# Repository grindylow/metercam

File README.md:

# MeterCam

A WiFi "webcam" to monitor gas/water/electricity meters, or anything else that
needs regular (daily/weekly/monthly) inspection. When set to weekly intervals,
MeterCam will run on one set of AAA batteries for many years.

## Introduction

The MeterCam combines a standard ESP32-CAM module [1] (which works great, but
consumes a lot of power, even when sleeping) with custom hardware that only
powers up the camera module when it wants to take a picture, for example once
a day/week.

This custom hardware utilises a very energy-efficient "high-side power switch"
and a low-power microcontroller - keeping the power consumption during sleep
periods below 1 µW and resulting in battery lifetimes of many years.

## Features

- [ ] Configurable WiFi SSID/password
- [ ] Extended configuration options
- [ ] Configuration change via MQTT
- [ ] Image output via MQTT
- [ ] image acquisition on boot
- [ ] enable/disable "flash" LED
- [ ] Streaming video over HTTP (for setup)
- [ ] request shutdown

## Setup Instructions

The configuration web interface is based around XYZ's WifiManager[...].

A virgin MeterCam will enter configuration mode when first powered up.

Connect to the MeterCam WiFi Access Point (SSID "METERCAM", password:
"metercam") and configure all parameters as desired.

From now on, MeterCam will wake up at the configured intervals (see
[below](#operation)).

@todo you can force a configured MeterCam to go back into configuration mode
by setting jumper JPx. MeterCam will also fall back to configuration mode if
it hasn't been able to connect to the configured WiFi network five times in a
row (this is a feature of WifiManager).

## Operation

No maintenance is required during regular operation. MeterCam will

 1. wake up every interval
 2. connect to the configured WiFi
 3. take a picture
 4. transmit this picture via the configured means (MQTT, E-Mail, FTP, etc.)
 5. go back to sleep

@todo If MQTT is enabled, the MeterCam will subscribe to the configured "inbox" topic
and interpret incoming configuration requests.

## Detailed Description of MeterCam Components

### MeterCam Printed Circuit Board (PCB)

The MeterCam PCB contains a Microchip PIC16 microcontroller. It communicates
with the ESP32-CAM module via a bidirectional serial link. This link allows the
ESP32-CAM to request power-off and specific sleep durations.

The microcontroller also controls a "high-side power switch" used to cut power
to the ESP32-CAM module - thereby preventing the ESP32-CAM from consuming any
power during periods of inactivity.

### MeterCam µC Firmware

The software running on the MeterCam's microcontroller performs the following
tasks:

 - [ ] On initial bootup, switch *on* ESP32-CAM module, then wait for shutdown
   command .
 - [ ] Switch *off* ESP32-CAM module after 20 seconds, even if no
   (shutdown) command was received. Use a default sleep time of approximately 1 day in this case, if now other time has previously been configured.
 - [ ] Switch *off* ESP32-CAM when requested (via serial connection), and sleep
   for requested duration, consuming as little power as possible.
 - [ ] Switch *on* ESP32-CAM when requested sleep duration has passed.

ESP32-Firmware and µC-Firmware communicate via serial ports. The µC acts as the
slave and will respond to the following commands when transmitted by the ESP32:

| Command | Reply | Explanation |
|---------|-------|-------------|
| 'E' | 'e' | Echo request/reply - for testing the connection |
| 'A' <HI> <LO> | 'a' <HI> <LO> | Set new sleep time in 'intervals'. |
| 'S' | 's' | Switch off power to ESP32 'now' and sleep for configured sleep duration |

### MeterCam ESP32-CAM Firmware

Compile using Arduino Studio with ESP extensions and the following libraries:
 - ESP32-CAM
 - [WifiManager](https://github.com/tzapu/WiFiManager)
 - -[DoubleResetDetect](https://github.com/jenscski/DoubleResetDetect)-
 - [EspMQTTClient](https://github.com/plapointe6/EspMQTTClient), which requires...
   - [MQTT PubSubClient](https://github.com/knolleary/pubsubclient)
 - [ArduinoJSON](https://arduinojson.org/)

[1] ESP32-CAM module: ...

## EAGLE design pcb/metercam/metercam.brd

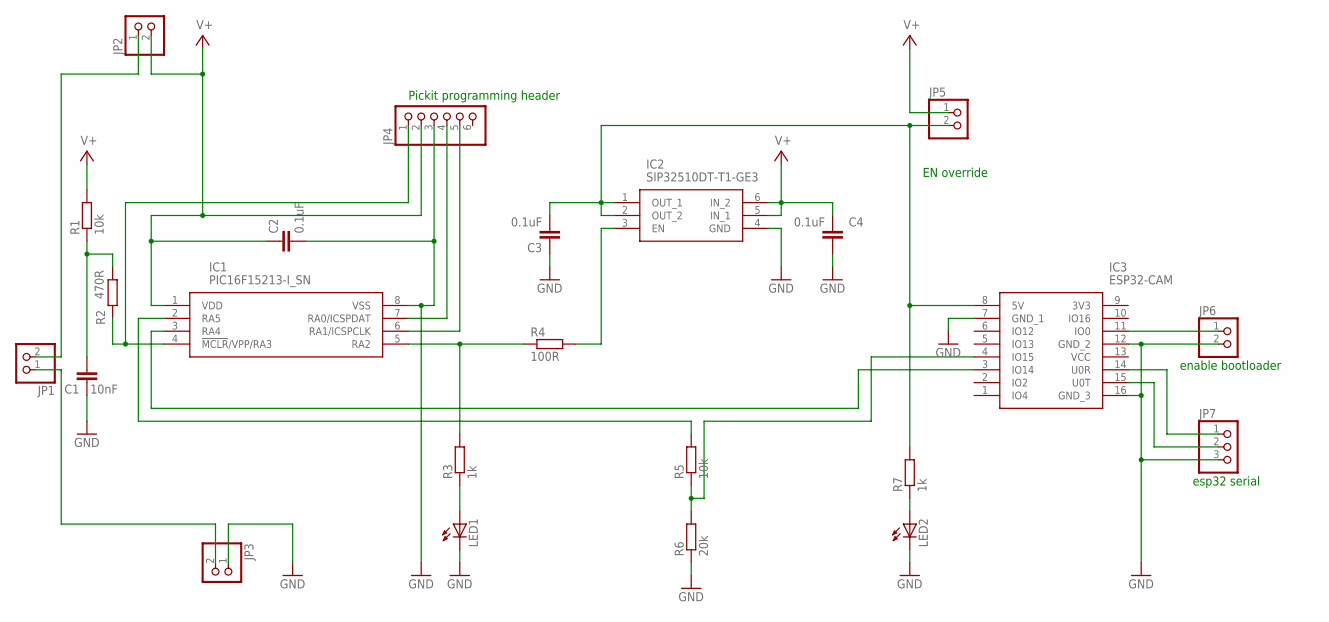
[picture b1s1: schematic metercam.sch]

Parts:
C1: 10nF; C0805
C2, C3, C4: 0.1uF; C0805
IC1: PIC16F15213-I_SN; SOIC127P600X175-8N
IC2: SIP32510DT-T1-GE3; SOT95P284X110-6N
IC3: ESP32-CAM; ESP32CAM
JP1, JP2, JP3, JP5, JP6: PINHD-1X2; 1X02
JP4: PINHD-1X6; 1X06
JP7: PINHD-1X3; 1X03
LED1, LED2: LEDSML0805; SML0805
R1, R5: 10k; R0805
R2: 470R; R0805
R3, R7: 1k; R0805
R4: 100R; R0805
R6: 20k; R0805

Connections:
GND: C1.1, C2.2, C3.1, C4.1, IC1.8 (VSS), IC2.4 (GND), IC3.7 (GND_1), IC3.12 (GND_2), IC3.16 (GND_3), JP3.1, JP4.3, JP6.2, JP7.3, LED1.C, LED2.C, R6.1
unnamed: IC1.4 (!MCLR!/VPP/RA3), JP4.1, R2.1
unnamed: IC3.14 (U0R), JP7.1
unnamed: JP1.2, JP2.1
unnamed: IC1.7 (RA0/ICSPDAT), JP4.4
unnamed: IC1.6 (RA1/ICSPCLK), JP4.5
unnamed: IC3.11 (IO0), JP6.1
unnamed: JP1.1, JP3.2
unnamed: IC3.15 (U0T), JP7.2
unnamed: IC1.5 (RA2), R3.2, R4.1
unnamed: IC2.3 (EN), R4.2
unnamed: C3.2, IC2.1 (OUT_1), IC2.2 (OUT_2), IC3.8 (5V), JP5.2, R7.2
unnamed: LED2.A, R7.1
unnamed: LED1.A, R3.1
unnamed: IC1.3 (RA4), IC3.3 (IO14)
unnamed: IC1.2 (RA5), R5.2
unnamed: IC3.4 (IO15), R5.1, R6.2
unnamed: C1.2, R1.1, R2.2
V+: C2.1, C4.2, IC1.1 (VDD), IC2.5 (IN_1), IC2.6 (IN_2), JP2.2, JP4.2, JP5.1, R1.2

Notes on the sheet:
Pickit programming header
enable bootloader
esp32 serial
EN override

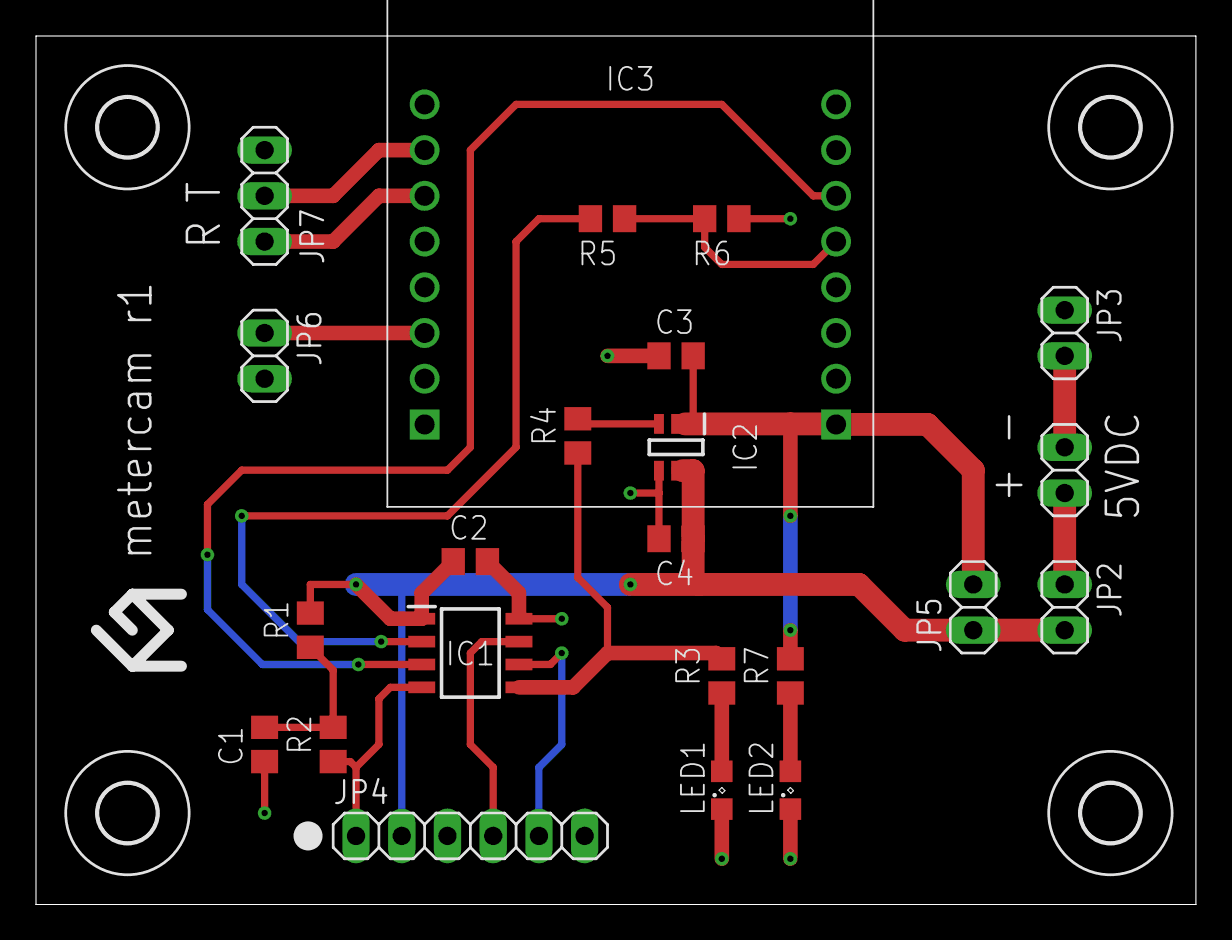
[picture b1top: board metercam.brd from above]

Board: 2 copper layers, 64.4 x 48.2 mm, 27 parts (0 on the bottom side), 19 nets.

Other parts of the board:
U$1, U$2, U$3, U$4: 3,2

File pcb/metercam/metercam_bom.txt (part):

Stückliste exportiert aus M:/2-Martin/20-homeWork/20 projects/2020-12 metercam/pcb/metercam/metercam.sch am 30.12.2020 21:32

Part Value             Device            Package            Description                                                          ARROW_PART_NUMBER ARROW_PRICE-STOCK DESCRIPTION                                                          HEIGHT MANUFACTURER_NAME MANUFACTURER_PART_NUMBER MOUSER_PART_NUMBER   MOUSER_PRICE-STOCK                                                                                                 
C1   10nF              C-EUC0805         C0805              CAPACITOR, European symbol                                                                                                                                                                                                                                                                                                                                              
C2   0.1uF             C-EUC0805         C0805              CAPACITOR, European symbol                                                                                                                                                                                                                                                                                                                                              
C3   0.1uF             C-EUC0805         C0805              CAPACITOR, European symbol                                                                                                                                                                                                                                                                                                                                              
C4   0.1uF             C-EUC0805         C0805              CAPACITOR, European symbol                                                                                                                                                                                                                                                                                                                                              
IC1  PIC16F15213-I_SN  PIC16F15213-I_SN  SOIC127P600X175-8N 8-bit Microcontrollers - MCU                                                                             8-bit Microcontrollers - MCU                                         1.75mm Microchip         PIC16F15213-I/SN         579-PIC16F15213-I/SN https://www.mouser.co.uk/ProductDetail/Microchip-Technology/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
IC2  SIP32510DT-T1-GE3 SIP32510DT-T1-GE3 SOT95P284X110-6N   VISHAY - SIP32510DT-T1-GE3 - IC, LOAD SWITCH, 1.1V-5.5V, 3A, TSOT-23                                     VISHAY - SIP32510DT-T1-GE3 - IC, LOAD SWITCH, 1.1V-5.5V, 3A, TSOT-23 1.1mm  Vishay            SIP32510DT-T1-GE3        78-SIP32510DT-T1-GE3 https://www.mouser.co.uk/ProductDetail/Vishay-Siliconix/SIP3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          
IC3  ESP32-CAM         ESP32-CAM         ESP32CAM           Modules PCBA Module RoHS                                                                                 Modules PCBA Module RoHS                                             5mm    Ai-Thinker        ESP32-CAM                                                                                                                                                        
JP1                    PINHD-1X2         1X02               PIN HEADER                                                                                                                                                                                                                                                                                                                                                              
JP2                    PINHD-1X2         1X02               PIN HEADER                                                                                                                                                                                                                                                                                                                                                              
JP3                    PINHD-1X2         1X02               PIN HEADER                                                                                                                                                                                                                                                                                                                                                              
JP4                    PINHD-1X6         1X06               PIN HEADER                                                                                                                                                                                                                                                                                                                                                              
JP5                    PINHD-1X2         1X02               PIN HEADER                                                                                                                                                                                                                                                                                                                                                              
JP6                    PINHD-1X2         1X02               PIN HEADER                                                                                                                                                                                                                                                                                                                                                              
JP7                    PINHD-1X3         1X03               PIN HEADER                                                                                                                                                                                                                                                                                                                                                              
LED1                   LEDSML0805        SML0805            LED                                                                                                                                                                                                                                                                                                                                                                     
LED2                   LEDSML0805        SML0805            LED                                                                                                                                                                                                                                                                                                                                                                     
R1   10k               R-EU_R0805        R0805              RESISTOR, European symbol                                                                                                                                                                                                                                                                                                                                               
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
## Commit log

2021-02-01 Initial commit of PCB and ESP32 sub-projects.
2021-02-02 Initial commit of MPLabX project containing the µC part of the metercam project.
2021-02-05 initial commit of metercam-rx, a simple MQTT-to-File converter
2021-02-06 react differently to jpg and info messages
2021-02-06 Added support for changing sleep duration.
2021-02-06 added support for "V" command
2024-11-09 renamed webserver component as it clashes with new library version
2025-01-10 added design notes and one datasheet
